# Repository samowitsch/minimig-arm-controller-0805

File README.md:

# Minimig-ARM-Controller-0805

Rebuild Minimig ARM Controller board using 0805 SMD components.

> ⚠️ IMPORTANT NOTICE! It seems that only the first rev 1 of my Minimig controller is working! See issue #1

## Preface

Thanks to [Dennis van Weeren](https://en.wikipedia.org/wiki/Minimig), Jakub Bednarski and all contributors for the great [Minimig](https://en.wikipedia.org/wiki/Minimig) project! 
_"Never give up, never surrender!"_ **;o)**

## Disclaimer

> Use/build this project/pcb at your own risk. I am a hobbyist and not an professional 
> electrician or pcb designer and not responsive for any damage to your Minimig.
> 
> By the way my version is not as smart and elegant like the original, i am just using 
> 4 layers instead of two ;o)

## Introduction

Me as a late starter to the Minimig project late 2020 wants to build a [Minimig](https://en.wikipedia.org/wiki/Minimig) to get again the Amiga feeling i 
had a couple of years ago where i owned the most models of the [Amiga](https://en.wikipedia.org/wiki/Amiga) family.

First i tried to solder the [ARM controller board](https://www.amigawiki.org/doku.php?id=de:expansion:storage:minimig_arm_controller) needed for the [Minimig](https://en.wikipedia.org/wiki/Minimig). I ment i was good in soldering but screwed up ;o)
Because of this defeat i decided to make a board using 0805 SMD components for easy hand soldering. And my eyes are also not the very best at all ;-)

## What is included in this repository?

* KiCad files
* Gerber files
* [Firmware files](/firmware/Readme.md)

## BOM

This rebuild pcb uses the same designators as the existing ARM controller.
To buy the parts for this board you can use the existing [a1k.org parts list](resources/minimig_arm_v11fix_bestueckung.pdf).
But instead of 0603 components you can use the larger 0805 smd components.

## How to flash the ARM Controller firmware

The needed firmware [you can find here](https://www.a1k.org/forum/index.php?threads/39601/) (requires registration) or in [this repository](/firmware/Readme.md).

### Flash standalone

1. Connect the TEST header pins with a jumper. Then power up the board with 3.3 V connected to the 
   DC pins (double check correct orientation!) for round about 7 - 10 seconds (see picture below). Shutdown the power again. 
   Remove the jumper from TEST header pins. The Atmel AT91SAM7S256 MCU should be now in usb programming mode.

2. Now connect the ARM controller with the USB cable to your pc. And power up the board again.

3. For example under Ubuntu you should see now a usb device **/dev/ttyACM0**. For 
   Ubuntu you need the [SAM-BA CDC 2.18](https://www.microchip.com/en-us/development-tool/SAM-BA-In-system-Programmer) ([Download](https://ww1.microchip.com/downloads/en/DeviceDoc/SAM-BA+v2.18+for+Linux.zip)) utility (maybe a newer version is working too).

4. When connected choose the bin firmware file and press "Send File".

5. In next dialoges for unlock/lock regions you can press "Ja"/"Yes" two times.

6. At the end you can verify if the flashing process where 
   successfully on pressing "Compare sent file with memory"

### Flash connected to Minimig

Should work in the same way as described above with the difference that the 
board is connected to the Minimig and get its power from there.

## Mounted ARM controller

## Running Minimig v1.1 with my version

## PCB Layers

Layer Nr | Comment
--- | ---
1 | Signal
2 | +1V8 plane VDDCORE
3 | +3V3 plane VDDIN
4 | GND plane/Signal

## Comparison between versions

0805 rev1.0.3 | 0805 rev1.0.2 | 0805 rev1 | original 0603 version
--- | --- | --- | ---
 |  |                | 
no stable | not stable | stable(?) |
changes: reset button, power led, smd resonator | changes: dont know anymore ;o) |  | What a beauty of a pcb design of Jakub!
 |  |  | 
 |  |  | 

## Resources and links

* [Original Minimig page](https://www.techtravels.org/wp-content/uploads/pefiles/minimig/weeren001/minimig.html)
* [Minimig on a1k.org](https://www.a1k.org/forum/index.php?forums/53/)
* [Minimig on amigawiki.org](https://www.amigawiki.org/doku.php?id=de:models:minimig)
* [Minimig on Wikipedia](https://en.wikipedia.org/wiki/Minimig)
* [Minimig on Illuwatar Design](http://www.illuwatar.se/)
* [Make: Poor man's Minimig ARM Controller](https://sweetlilmre.blogspot.com/2013/05/make-poor-mans-minimig-arm-controller.html)
* [An FPPGA based Amiga – The Minimig](https://theretrohacker.com/2022/12/20/an-fppga-based-amiga-the-minimig/)
* [cristianoag/minimig](https://github.com/cristianoag/minimig)
* [wiretap-retro/MigStorm-ITX](https://github.com/wiretap-retro/MigStorm-ITX)
* [minimig.ca](https://www.minimig.ca/index.php/software/)
* [0805 Minimig Arm Controller on MigStorm ITX](https://youtu.be/l10HLR_F88E?si=PKMIdRAqAoQ9IPDd&t=572)

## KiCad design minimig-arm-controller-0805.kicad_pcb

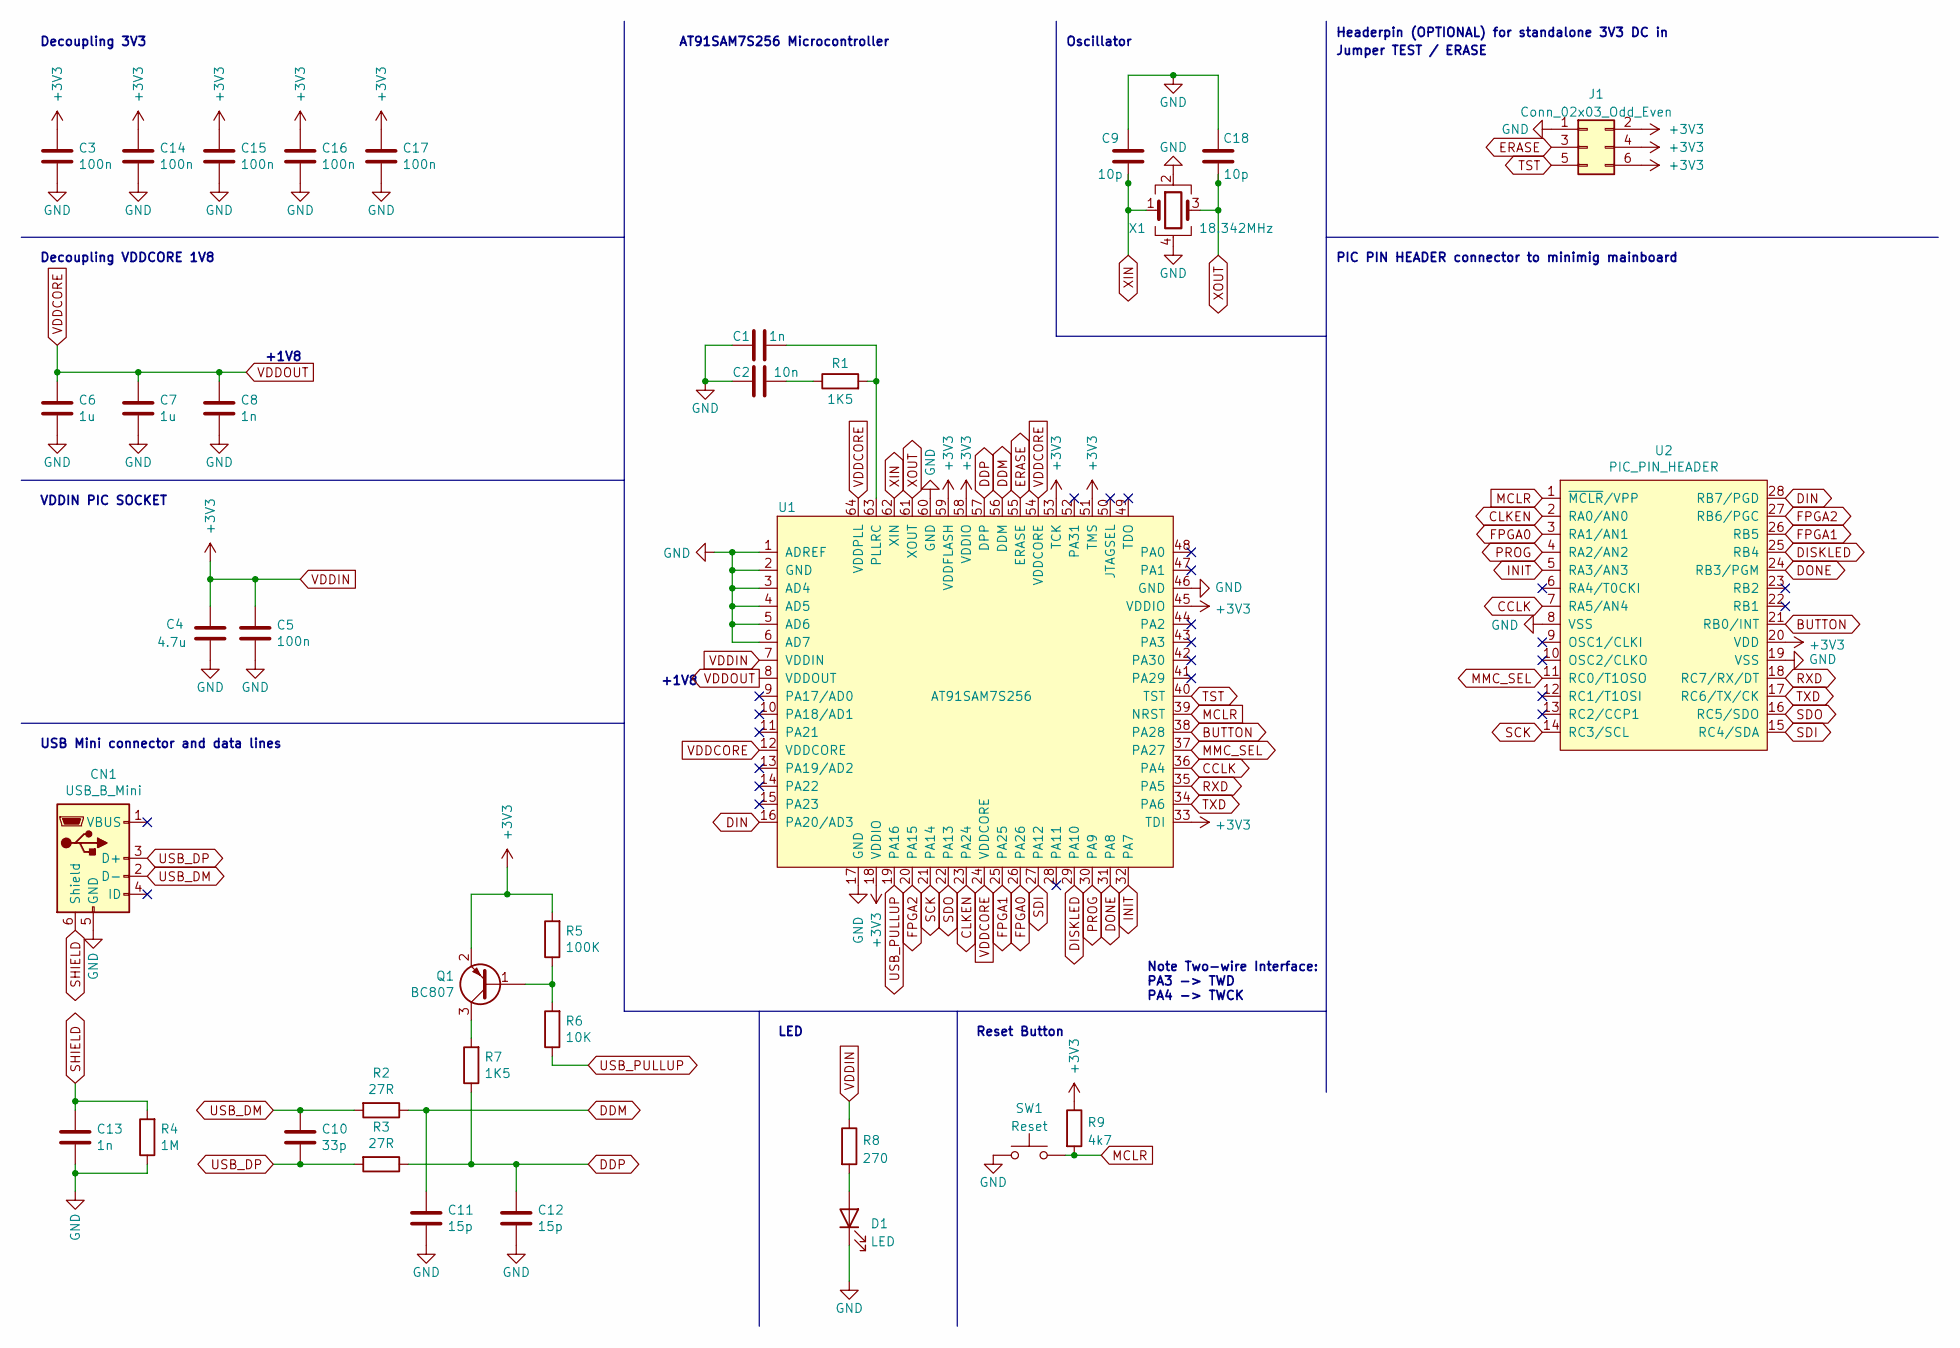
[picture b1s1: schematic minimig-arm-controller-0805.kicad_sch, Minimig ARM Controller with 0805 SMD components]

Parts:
C1, C8, C13: 1n; C_0805_2012Metric_Pad1.18x1.45mm_HandSolder
C2: 10n; C_0805_2012Metric_Pad1.18x1.45mm_HandSolder
C3, C5, C14, C15, C16, C17: 100n; C_0805_2012Metric_Pad1.18x1.45mm_HandSolder
C4: 4.7u; C_1206_3216Metric_Pad1.33x1.80mm_HandSolder
C6, C7: 1u; C_0805_2012Metric_Pad1.18x1.45mm_HandSolder
C9, C18: 10p; C_0805_2012Metric_Pad1.18x1.45mm_HandSolder
C10: 33p; C_0805_2012Metric_Pad1.18x1.45mm_HandSolder
C11, C12: 15p; C_0805_2012Metric_Pad1.18x1.45mm_HandSolder
CN1: USB_B_Mini; USB_Mini-B_Wuerth_65100516121_Horizontal
D1: LED; C_0805_2012Metric_Pad1.18x1.45mm_HandSolder
J1: Conn_02x03_Odd_Even; PinHeader_2x03_P2.54mm_Vertical
Q1: BC807; SOT-23
R1, R7: 1K5; R_0805_2012Metric_Pad1.20x1.40mm_HandSolder
R2, R3: 27R; R_0805_2012Metric_Pad1.20x1.40mm_HandSolder
R4: 1M; R_0805_2012Metric_Pad1.20x1.40mm_HandSolder
R5: 100K; R_0805_2012Metric_Pad1.20x1.40mm_HandSolder
R6: 10K; R_0805_2012Metric_Pad1.20x1.40mm_HandSolder
R8: 270; C_0805_2012Metric_Pad1.18x1.45mm_HandSolder
R9: 4k7; R_0805_2012Metric_Pad1.20x1.40mm_HandSolder
SW1: Reset; SW_Tactile_SPST_Angled_PTS645Vx39-2LFS
U1: AT91SAM7S256; LQFP-64_10x10mm_P0.5mm
U2: PIC_PIN_HEADER; DIP-28_W7.62mm_Socket
X1: 18.342MHz; Crystal_SMD_3225-4Pin_3.2x2.5mm

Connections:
BUTTON: U1.38 (PA28), U2.21 (RB0/INT)
CCLK: U1.36 (PA4), U2.7 (RA5/AN4)
CLKEN: U1.23 (PA24), U2.2 (RA0/AN0)
DDM: C11.1, R2.1, U1.56 (DDM)
DDP: C12.1, R3.1, R7.1, U1.57 (DPP)
DIN: U1.16 (PA20/AD3), U2.28 (RB7/PGD)
DISKLED: U1.29 (PA10), U2.25 (RB4)
DONE: U1.31 (PA8), U2.24 (RB3/PGM)
ERASE: J1.3, U1.55 (ERASE)
FPGA0: U1.26 (PA26), U2.3 (RA1/AN1)
FPGA1: U1.25 (PA25), U2.26 (RB5)
FPGA2: U1.20 (PA15), U2.27 (RB6/PGC)
GND: C1.2, C2.2, C3.2, C4.2, C5.2, C6.2, C7.2, C8.2, C9.2, C11.2, C12.2, C13.2, C14.2, C15.2, C16.2, C17.2, C18.2, CN1.5 (GND), D1.1 (K), J1.1, R4.1, SW1.1, U1.1 (ADREF), U1.2 (GND), U1.3 (AD4), U1.4 (AD5), U1.5 (AD6), U1.6 (AD7), U1.17 (GND), U1.46 (GND), U1.60 (GND), U2.8 (VSS), U2.19 (VSS), X1.2, X1.4
INIT: U1.32 (PA7), U2.5 (RA3/AN3)
MCLR: R9.2, SW1.2, U1.39 (NRST), U2.1 (~MCLR/VPP)
MMC_SEL: U1.37 (PA27), U2.11 (RC0/T1OSO)
unnamed: C1.1, R1.2, U1.63 (PLLRC)
unnamed: C2.1, R1.1
unnamed: D1.2 (A), R8.2
unnamed: Q1.1 (B), R5.1, R6.2
unnamed: Q1.3 (C), R7.2
PROG: U1.30 (PA9), U2.4 (RA2/AN2)
RXD: U1.35 (PA5), U2.18 (RC7/RX/DT)
SCK: U1.21 (PA14), U2.14 (RC3/SCL)
SDI: U1.27 (PA12), U2.15 (RC4/SDA)
SDO: U1.22 (PA13), U2.16 (RC5/SDO)
SHIELD: C13.1, CN1.6 (Shield), R4.2
TST: J1.5, U1.40 (TST)
TXD: U1.34 (PA6), U2.17 (RC6/TX/CK)
USB_DM: C10.1, CN1.2 (D-), R2.2
USB_DP: C10.2, CN1.3 (D+), R3.2
USB_PULLUP: R6.1, U1.19 (PA16)
VDDCORE: C6.1, C7.1, C8.1, U1.8 (VDDOUT), U1.12 (VDDCORE), U1.24 (VDDCORE), U1.54 (VDDCORE), U1.64 (VDDPLL)
VDDIN: C3.1, C4.1, C5.1, C14.1, C15.1, C16.1, C17.1, J1.2, J1.4, J1.6, Q1.2 (E), R5.2, R8.1, R9.1, U1.7 (VDDIN), U1.18 (VDDIO), U1.33 (TDI), U1.45 (VDDIO), U1.51 (TMS), U1.53 (TCK), U1.58 (VDDIO), U1.59 (VDDFLASH), U2.20 (VDD)
XIN: C9.1, U1.62 (XIN), X1.1
XOUT: C18.1, U1.61 (XOUT), X1.3

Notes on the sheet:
Decoupling VDDCORE 1V8
LED
USB Mini connector and data lines
Headerpin (OPTIONAL) for standalone 3V3 DC in
VDDIN PIC SOCKET
PIC PIN HEADER connector to minimig mainboard
+1V8
Oscillator
Jumper TEST / ERASE
Decoupling 3V3
Note Two-wire Interface: PA3 -> TWD PA4 -> TWCK
Reset Button
AT91SAM7S256 Microcontroller

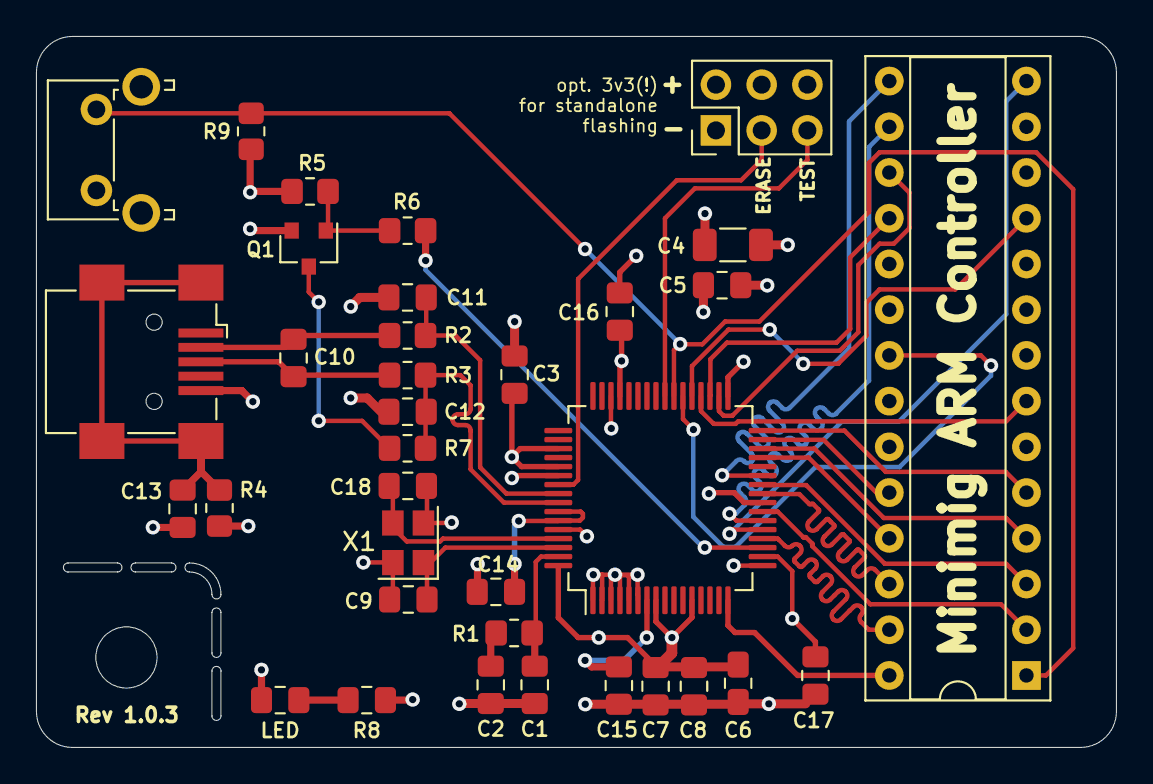
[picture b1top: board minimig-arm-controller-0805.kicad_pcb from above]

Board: 4 copper layers, 60.0 x 39.5 mm, 35 parts (0 on the bottom side), 36 nets.

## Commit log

2021-01-26 add KiCad project files
2021-01-27 changed README
2021-01-27 added original ARM Controller files
2021-01-27 fix wording
2021-02-03 changed readme.
2021-02-10 add text info to schematic about TWI(I2C) pins
2021-05-22 use handsoldering footprint for HC49-SD crystal
2022-02-16 rev1.0.2: some minor changes. change HC49 to THT
2022-02-16 remove and gitignore kicad backups
2022-02-16 add firmware. readme adaptions.
2022-02-16 add rev1.0.2 pictures
2022-02-16 picture changes
2022-02-16 fix dpi
2022-02-17 rev1.0.3 reroute some stuff
2023-06-02 Update README.md
    add additional resource links about minimig
2023-06-23 added warning/notive about later pcb revisions that are not working. Dont know why at the moment ;o(
2023-07-08 add gcc-arm-none-eabi-4_8-2014q1-20140314-linux.tar.bz2, ar, and 4479 more files...
2023-07-08 change path in makefile for gcc-arm-none-eabi-4_8-2014q1
2023-07-08 add .gitignore. add compiled files.
2023-07-15 add resources about AT91SAM7S
2023-07-15 update readme and pictures
2023-07-15 latest pcb changes
2023-07-15 latest rev. fix detached head and merge conflict.
2023-07-18 fix label
2023-07-18 small fix after DRC
2023-07-18 add doc6175.pdf
